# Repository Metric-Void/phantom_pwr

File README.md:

# Phantom Power Supply
## Description
This is a standalone power supply for phantom power microphones. 48V Phantom power is "injected" into the wire to power the microphone, and the output can be directly sent to computers, phones, etc.

Power supply range is 12V-19V by design. Voltages close to this may work, but not guaranteed. The DC-DC converter circuit is designed to output 0.5A, well above the requirement for a single microphone. The circuit can be expanded to supply more microphones.

## Usage
This project is designed with Autodesk EAGLE PCB. Free versions would be enough since it have only one schematic and one board. Simply clone into your Documents/EAGLE/projects folder, and open the epf file.

The completed circuit board should be placed in a shielded, metal enclosure to prevent noise.

## Licence
NO WARRANTY OF ANY KIND. Free for educational and hobbyist use. Contact for commercial use.

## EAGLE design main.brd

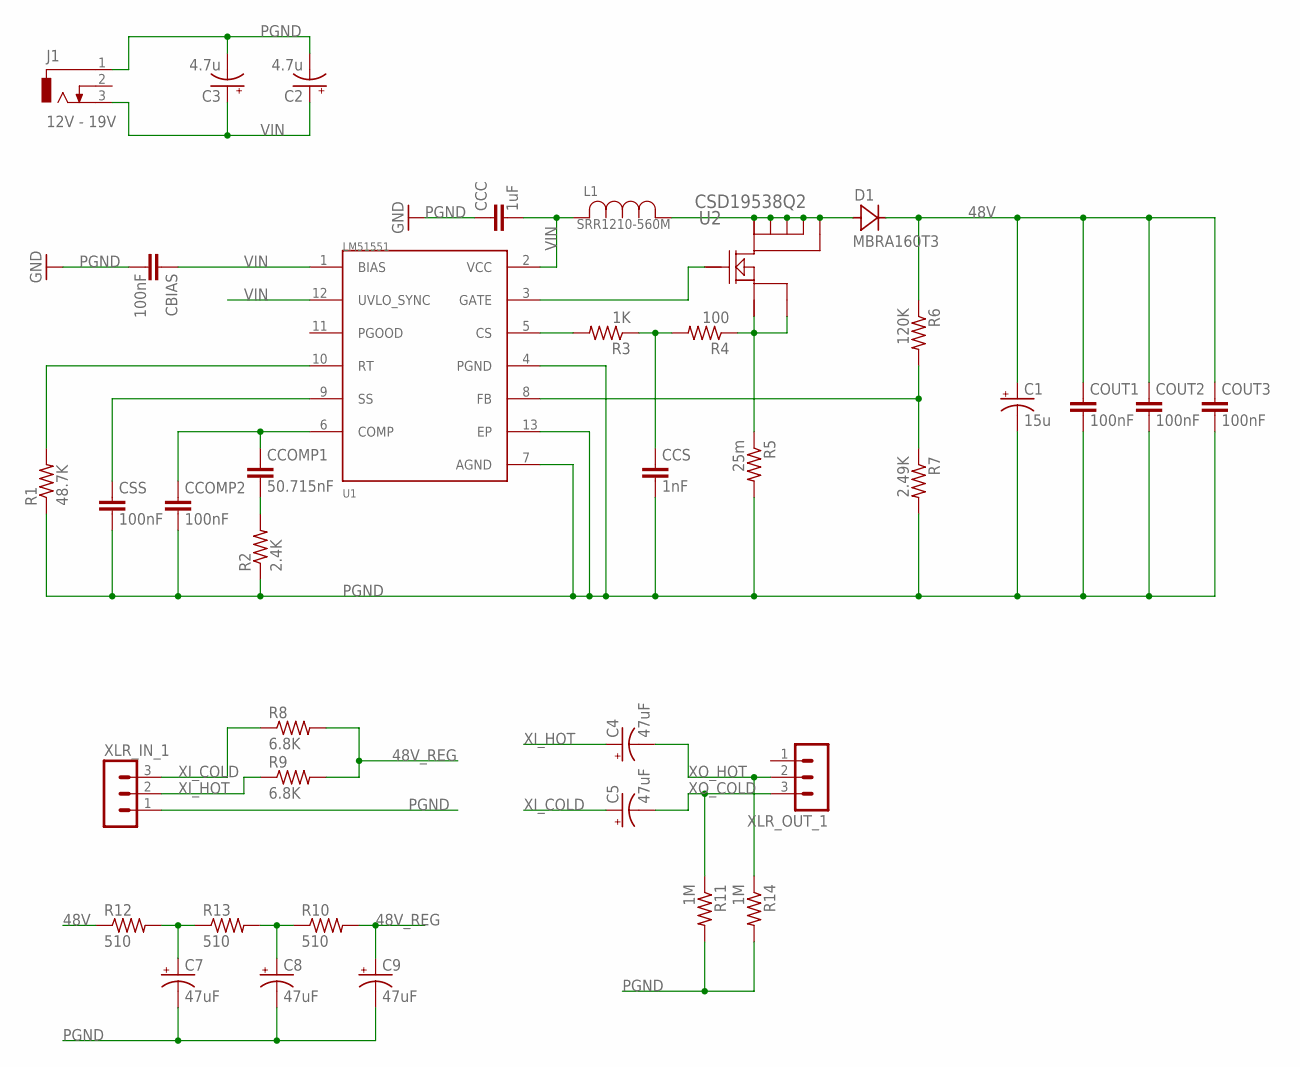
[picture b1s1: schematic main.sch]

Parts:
C1: 15u; CT7343
C2, C3: 4.7u; CT7343
C4, C5, C7, C8, C9: 47uF; 153CLV-0810
CBIAS: 100nF; C0805
CCC: 1uF; C0805
CCOMP1: 50.715nF; C0805
CCOMP2: 100nF; C0805
CCS: 1nF; C0805
COUT1, COUT2, COUT3: 100nF; C0805
CSS: 100nF; C0805
D1: MBRA160T3; SMA
J1: 12V - 19V; DCJ0303
L1: SRR1210-560M; IND_BOURNS_SRR1210
R1: 48.7K; R0805
R2: 2.4K; R0805
R3: 1K; R0805
R4: 100; R0805
R5: 25m; R1206
R6: 120K; R0805
R7: 2.49K; R0805
R8, R9: 6.8K; R1206
R10, R12, R13: 510; R1206
R11, R14: 1M; R0805
U1: LM51551; SON45P300X300X80-13N
U2: CSD19538Q2; DQK0006C
XLR_IN_1: MA03-1
XLR_OUT_1: MA03-1

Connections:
48V: C1.+, COUT1.1, COUT2.1, COUT3.1, D1.C, R6.1, R12.1
48V_REG: C9.+, R8.2, R9.2, R10.2
unnamed: R1.2, U1.10 (RT)
unnamed: CSS.1, U1.9 (SS)
unnamed: CCOMP1.2, R2.2
unnamed: CCOMP1.1, CCOMP2.1, U1.6 (COMP)
unnamed: R4.1, R5.1, U2.4 (SOURCE_2), U2.7 (SOURCE_1)
unnamed: R3.2, U1.5 (CS)
unnamed: CCS.1, R3.1, R4.2
unnamed: U1.3 (GATE), U2.3 (GATE)
unnamed: D1.A, L1.1, U2.1 (DRAIN_1), U2.2 (DRAIN_2), U2.5 (DRAIN_3), U2.6 (DRAIN_4), U2.8 (DRAIN_5)
unnamed: R6.2, R7.1, U1.8 (FB)
unnamed: C8.+, R10.1, R13.2
unnamed: C7.+, R12.2, R13.1
PGND: C1.-, C2.-, C3.-, C7.-, C8.-, C9.-, CBIAS.2, CCC.1, CCOMP2.2, CCS.2, COUT1.2, COUT2.2, COUT3.2, CSS.2, J1.1, R1.1, R2.1, R5.2, R7.2, R11.2, R14.2, U1.4 (PGND), U1.7 (AGND), U1.13 (EP), XLR_IN_1.1
VIN: C2.+, C3.+, CBIAS.1, CCC.2, J1.3, L1.2, U1.1 (BIAS), U1.2 (VCC), U1.12 (UVLO_SYNC)
XI_COLD: C5.+, R8.1, XLR_IN_1.3
XI_HOT: C4.+, R9.1, XLR_IN_1.2
XO_COLD: C5.-, R11.1, XLR_OUT_1.3
XO_HOT: C4.-, R14.1, XLR_OUT_1.2

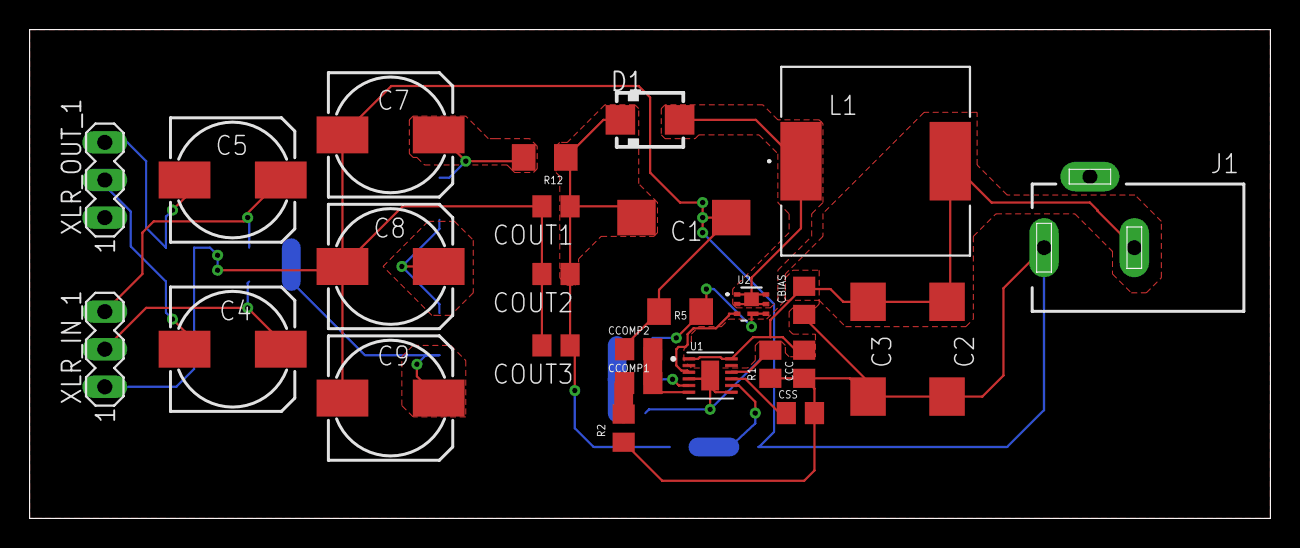
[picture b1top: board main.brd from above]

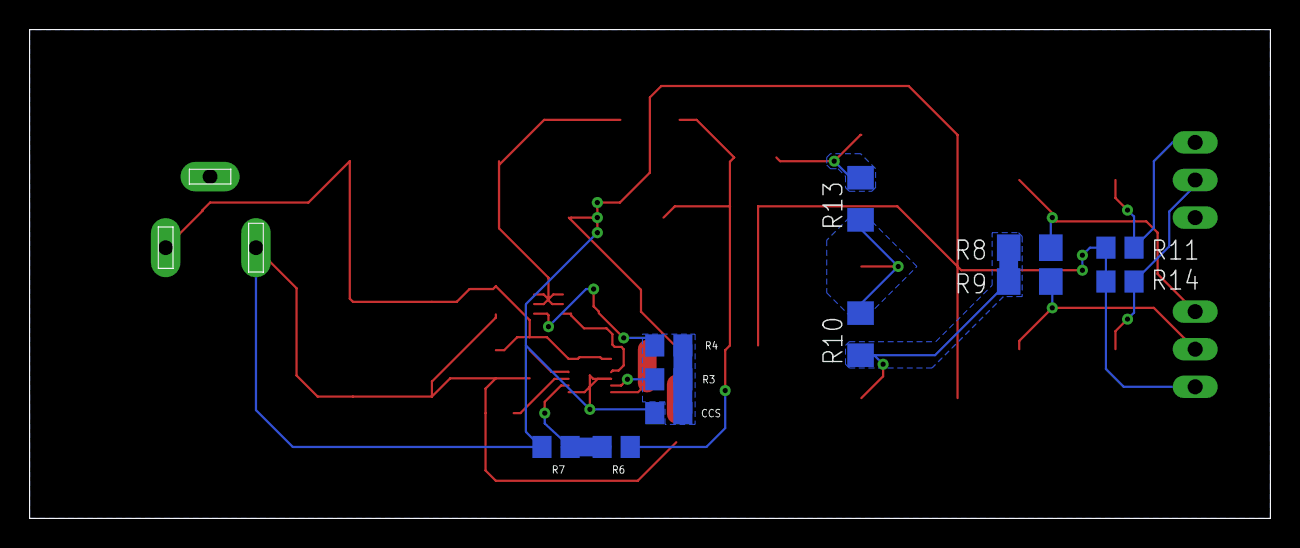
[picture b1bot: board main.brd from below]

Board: 2 copper layers, 83.8 x 33.0 mm, 38 parts (11 on the bottom side), 20 nets.

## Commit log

2019-12-07 Fixed README
